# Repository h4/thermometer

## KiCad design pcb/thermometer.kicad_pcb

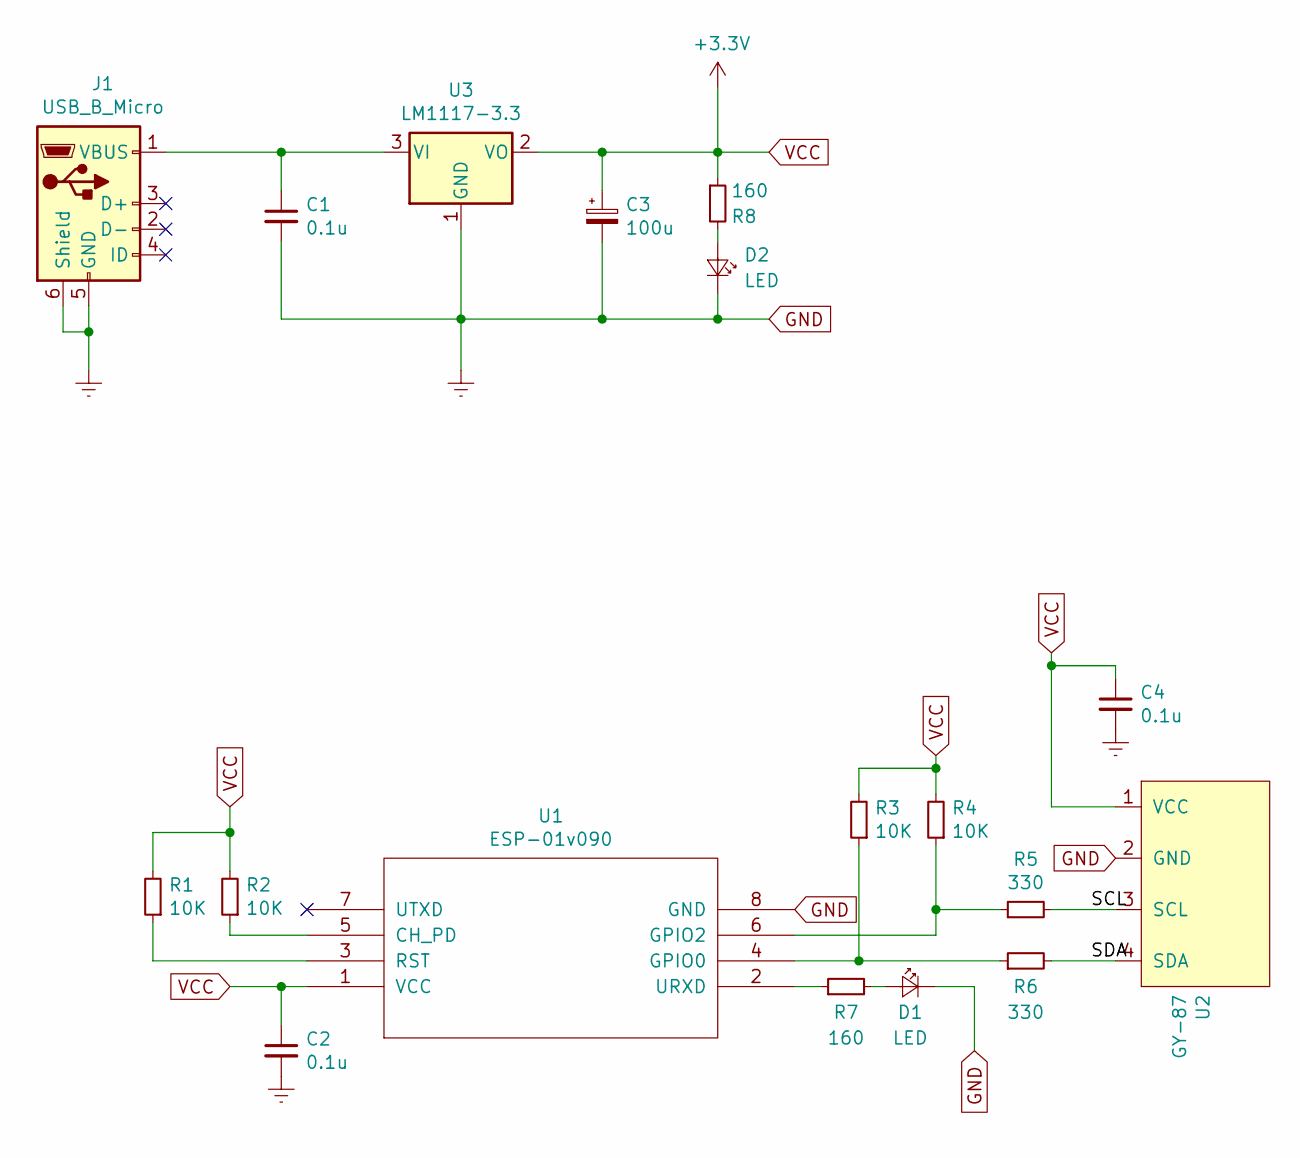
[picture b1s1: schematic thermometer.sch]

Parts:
C1, C2, C4: 0.1u; C_0603_1608Metric_Pad1.05x0.95mm_HandSolder
C3: 100u; CP_EIA-7343-31_Kemet-D_Pad2.25x2.55mm_HandSolder
D1, D2: LED; LED_0805_2012Metric_Pad1.15x1.40mm_HandSolder
J1: USB_B_Micro; USB_Micro-B_Molex_47346-0001
R1, R2, R3, R4: 10K; R_0603_1608Metric_Pad1.05x0.95mm_HandSolder
R5, R6: 330; R_0603_1608Metric_Pad1.05x0.95mm_HandSolder
R7, R8: 160; R_0603_1608Metric_Pad1.05x0.95mm_HandSolder
U1: ESP-01v090; PinSocket_2x04_P2.54mm_Vertical
U2: GY-87; gy-87
U3: LM1117-3.3; SOT-223-3_TabPin2

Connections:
/SCL: R5.2, U2.3 (SCL)
/SDA: R6.2, U2.4 (SDA)
GND: C1.2, C2.2, C3.2, C4.2, D1.1 (K), D2.1 (K), J1.5 (GND), J1.6 (Shield), U1.8 (GND), U2.2 (GND), U3.1 (GND)
unnamed: C1.1, J1.1 (VBUS), U3.3 (VI)
unnamed: D1.2 (A), R7.2
unnamed: D2.2 (A), R8.2
unnamed: R1.1, U1.3 (RST)
unnamed: R2.1, U1.5 (CH_PD)
unnamed: R3.1, R6.1, U1.4 (GPIO0)
unnamed: R4.1, R5.1, U1.6 (GPIO2)
unnamed: R7.1, U1.2 (URXD)
VCC: C2.1, C3.1, C4.1, R1.2, R2.2, R3.2, R4.2, R8.1, U1.1 (VCC), U2.1 (VCC), U3.2 (VO)

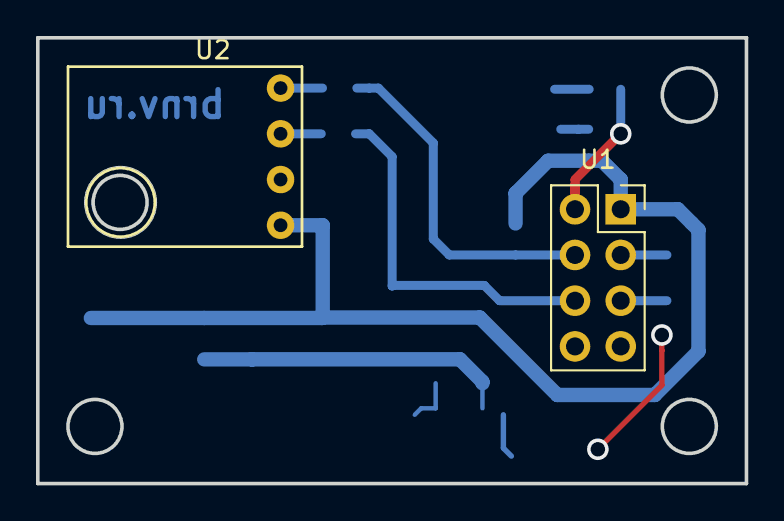
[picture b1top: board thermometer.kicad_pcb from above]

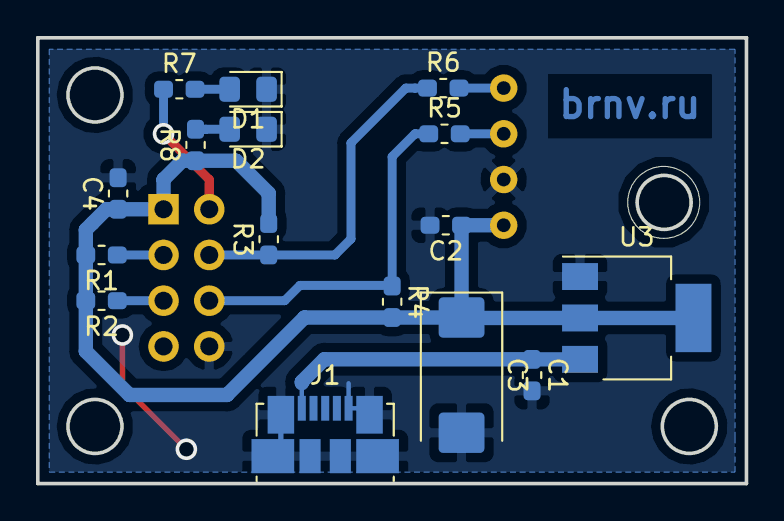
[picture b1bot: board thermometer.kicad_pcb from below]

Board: 2 copper layers, 39.4 x 24.8 mm, 18 parts (16 on the bottom side), 12 nets.

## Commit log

2019-02-17 Iinitial commit
2019-02-17 Add config page
2019-02-18 Store settings into EEPROM
2019-03-10 Simplify codebase
2019-04-08 Update gitignore
2019-04-08 Update PCB
2019-04-08 Remove degree symbol
